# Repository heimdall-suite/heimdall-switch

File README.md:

# heimdall-switch

Wireless power switch node for RC vehicles, part of the [Heimdall Suite](../heimdall-kickoff.md).

Controlled from `heimdall-module` over BLE, independent of the vehicle's
normal RC control link (e.g. CRSF) — this switch has its own out-of-band
radio path so it keeps working regardless of the state of the main control
link. It originated as a replacement for a boat's Jeti SPS-20 magnetic
switch, but is built as a generic building block (not a single-purpose
commercial part like Jeti's RCPS10) so the same design serves any RC
vehicle — boat, plane, car — needing a remotely switched load.

## How it's triggered

```mermaid
flowchart LR
    TX["EdgeTX transmitter<br/>Lua widget or OneClick"]
    BTN["Local button<br/>on the switch node"]
    MOD["heimdall-module<br/>external RF module (ESP32-C3)"]
    SW["heimdall-switch<br/>nRF52 node"]
    LOAD["Switched load"]

    TX -- "S.Port" --> MOD
    MOD -- "BLE command (absolute ON/OFF)" --> SW
    SW -- "MOSFET (fail-on)" --> LOAD
    SW -- "BLE ack burst" --> MOD
    MOD -- "S.Port telemetry (ack)" --> TX
    BTN -. "5-15s: toggle, 15s+: pair" .-> SW
```

The transmitter side (Lua widget or a OneClick action) sends the command
through `heimdall-module`, the external RF module in the transmitter's
module bay; `heimdall-module` relays it over BLE to `heimdall-switch`,
which drives the MOSFET and acks back the same path so the widget can
show "Hello" / "Goodbye" / "No response". The node also has a local button
for manual toggling and pairing, independent of that whole chain.

## Docs

- [.docs/hardware.md](.docs/hardware.md) — MCU, power, switching stage,
  feedback, button/LED, open hardware items
- [.docs/protocol.md](.docs/protocol.md) — BLE roles, pairing, runtime
  cycle, command/ack frame layouts, the transmitter-side Lua widget
- [.docs/persistence.md](.docs/persistence.md) — what's kept in flash
  across power loss (state + replay counter) and the wear-levelling scheme
- [.agents/AGENTS.md](.agents/AGENTS.md) / [CLAUDE.md](CLAUDE.md) —
  instructions for AI coding agents working in this repo
- [hardware/kicad/](hardware/kicad/) — first-draft KiCad schematic (see
  `.docs/hardware.md`'s Schematic section for what's in it and what's
  still a placeholder)

## Status

No firmware yet. nRF52 toolchain (nRF5 SDK vs. nRF Connect SDK/Zephyr vs.
upstream Zephyr) is not yet decided. `src/` is a placeholder until that's
settled. A first-pass schematic exists under `hardware/kicad/`.

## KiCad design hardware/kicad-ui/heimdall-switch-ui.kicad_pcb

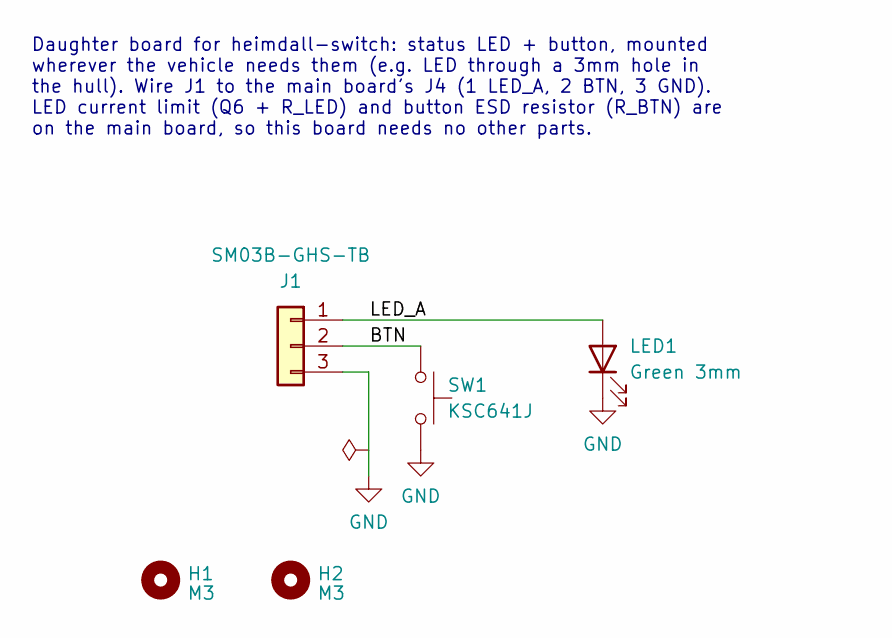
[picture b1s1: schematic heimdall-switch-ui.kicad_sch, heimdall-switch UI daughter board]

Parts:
H1, H2: M3; MountingHole_2.5mm_M3_Tapped
J1: SM03B-GHS-TB; JST_GH_SM03B-GHS-TB_1x03-1MP_P1.25mm_Horizontal; MPN SM03B-GHS-TB(LF)(SN); LCSC C514175
LED1: Green 3mm; LED_D3.0mm; MPN L-7104ZGCK; LCSC C414645
SW1: KSC641J; SW_Push_1P1T_NO_CK_KSC6xxJ; MPN KSC641J LFS; LCSC C226344

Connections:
/BTN: J1.2, SW1.1
/LED_A: J1.1, LED1.2 (A)
GND: J1.3, LED1.1 (K), SW1.2

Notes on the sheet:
Daughter board for heimdall-switch: status LED + button, mounted wherever the vehicle needs them (e.g. LED through a 3mm hole in the hull). Wire J1 to the main board's J4 (1 LED_A, 2 BTN, 3 GND). LED current limit (Q6 + R_LED) and button ESD resistor (R_BTN) are on the main board, so this board nee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

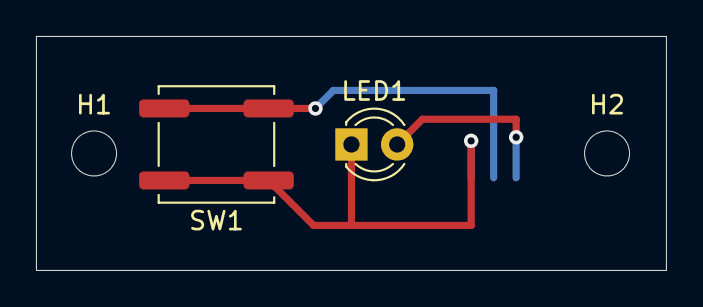
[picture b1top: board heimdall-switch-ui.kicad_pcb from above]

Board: 2 copper layers, 35.0 x 13.0 mm, 5 parts (1 on the bottom side), 3 nets.

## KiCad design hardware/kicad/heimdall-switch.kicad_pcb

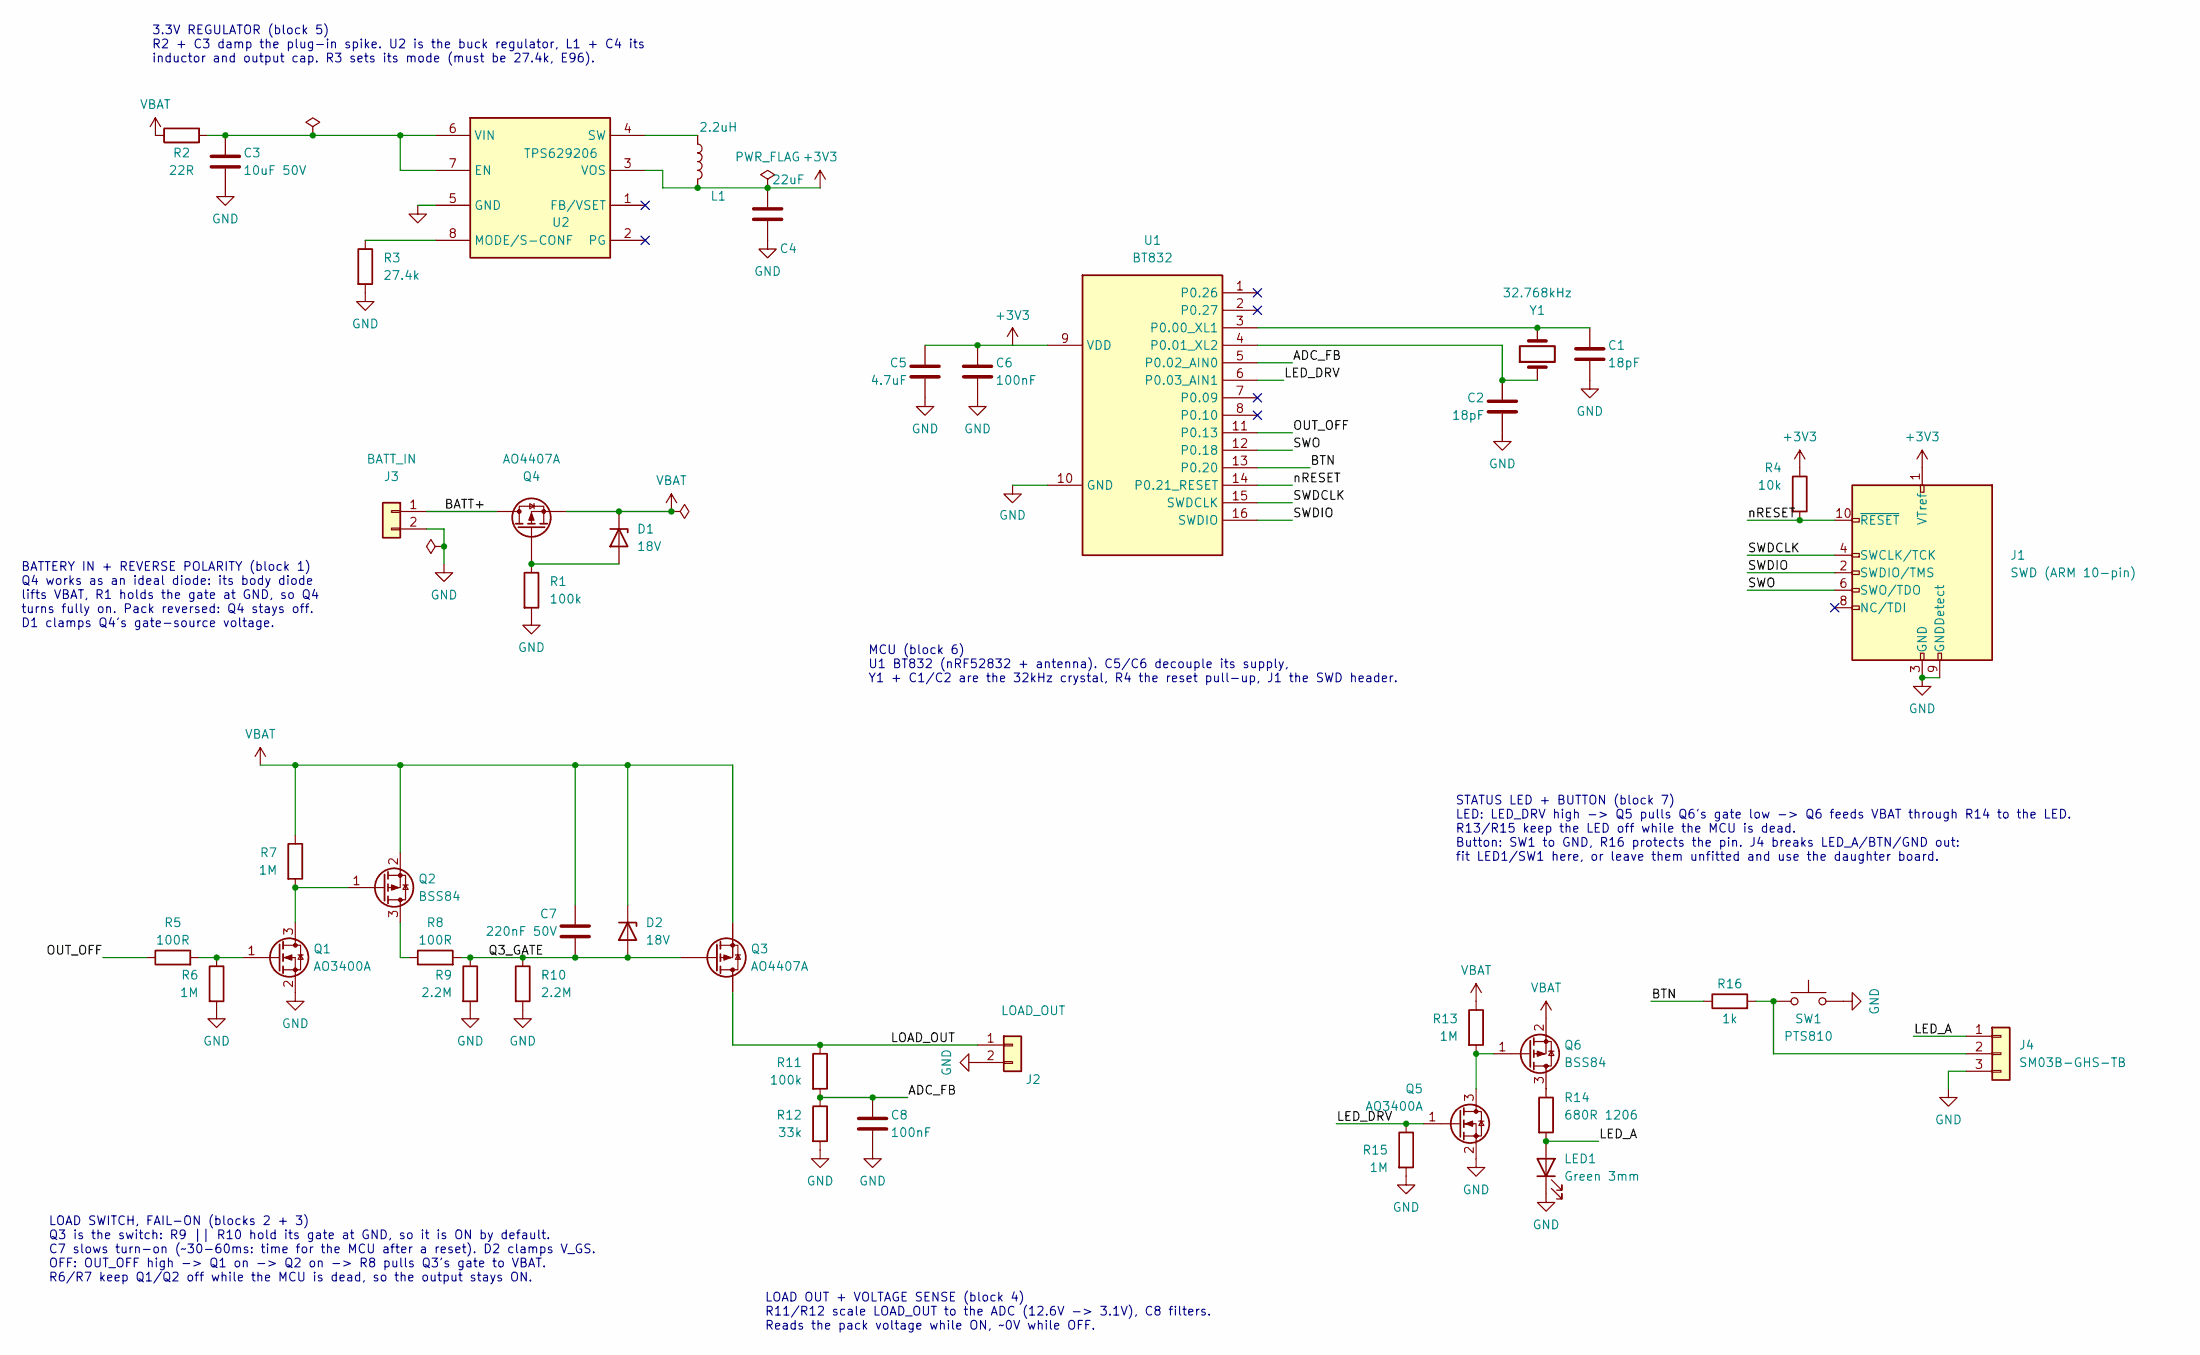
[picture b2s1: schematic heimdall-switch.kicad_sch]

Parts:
C1, C2: 18pF; C_0603_1608Metric; LCSC C1647
C3: 10uF 50V; C_1206_3216Metric; LCSC C89632
C4: 22uF; C_0805_2012Metric; LCSC C45783
C5: 4.7uF; C_0603_1608Metric; LCSC C19666
C6, C8: 100nF; C_0603_1608Metric; LCSC C14663
C7: 220nF 50V; C_0805_2012Metric; LCSC C5378
D1, D2: 18V; D_SOD-123; LCSC C2127
J1: SWD (ARM 10-pin); PinHeader_2x05_P1.27mm_Vertical_SMD; LCSC C41376037
J2: LOAD_OUT; SolderWire-0.75sqmm_1x02_P3.5mm_D1.25mm_OD2.3mm
J3: BATT_IN; SolderWire-0.75sqmm_1x02_P3.5mm_D1.25mm_OD2.3mm
J4: SM03B-GHS-TB; JST_GH_SM03B-GHS-TB_1x03-1MP_P1.25mm_Horizontal; LCSC C514175
L1: 2.2uH; L_1008_2520Metric; LCSC C237482
LED1: Green 3mm; LED_D3.0mm; LCSC C414645
Q1, Q5: AO3400A; SOT-23; LCSC C20917
Q2, Q6: BSS84; SOT-23; LCSC C493579
Q3, Q4: AO4407A; SOIC-8_3.9x4.9mm_P1.27mm; LCSC C16072
R1, R11: 100k; R_0603_1608Metric; LCSC C25803
R2: 22R; R_0603_1608Metric; LCSC C23345
R3: 27.4k; R_0603_1608Metric; LCSC C22964
R4: 10k; R_0603_1608Metric; LCSC C98220
R5, R8: 100R; R_0603_1608Metric; LCSC C22775
R6, R7, R13, R15: 1M; R_0603_1608Metric; LCSC C22935
R9, R10: 2.2M; R_0603_1608Metric; LCSC C22938
R12: 33k; R_0603_1608Metric; LCSC C4216
R14: 680R 1206; R_1206_3216Metric; LCSC C17975
R16: 1k; R_0603_1608Metric; LCSC C21190
SW1: PTS810; SW_SPST_PTS810; LCSC C116501
U1: BT832; Fanstel_BT832
U2: TPS629206; SOT-583-8; LCSC C5219292
Y1: 32.768kHz; Crystal_SMD_3215-2Pin_3.2x1.5mm; LCSC C32346

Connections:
+3V3: C4.1, C5.1, C6.1, J1.1 (VTref), L1.2, R4.1, U1.9 (VDD), U2.3 (VOS)
/ADC_FB: C8.1, R11.2, R12.1, U1.5 (P0.02_AIN0)
/BATT+: J3.1, Q4.5 (D), Q4.6 (D), Q4.7 (D), Q4.8 (D)
/BTN: R16.1, U1.13 (P0.20)
/LED_A: J4.1, LED1.2 (A), R14.2
/LED_DRV: Q5.1 (G), R15.1, U1.6 (P0.03_AIN1)
/LOAD_OUT: J2.1, Q3.5 (D), Q3.6 (D), Q3.7 (D), Q3.8 (D), R11.1
/OUT_OFF: R5.1, U1.11 (P0.13)
/Q3_GATE: C7.2, D2.2 (A), Q3.4 (G), R8.2, R9.1, R10.1
/SWDCLK: J1.4 (SWCLK/TCK), U1.15 (SWDCLK)
/SWDIO: J1.2 (SWDIO/TMS), U1.16 (SWDIO)
/SWO: J1.6 (SWO/TDO), U1.12 (P0.18)
/nRESET: J1.10 (~RESET), R4.2, U1.14 (P0.21_RESET)
GND: C1.2, C2.2, C3.2, C4.2, C5.2, C6.2, C8.2, J1.3 (GND), J1.5 (GND), J1.9 (GNDDetect), J2.2, J3.2, J4.3, LED1.1 (K), Q1.2 (S), Q5.2 (S), R1.2, R3.2, R6.2, R9.2, R10.2, R12.2, R15.2, SW1.2, U1.10 (GND), U2.5 (GND)
unnamed: D1.2 (A), Q4.4 (G), R1.1
unnamed: J4.2, R16.2, SW1.1
unnamed: Q1.3 (D), Q2.1 (G), R7.2
unnamed: Q1.1 (G), R5.2, R6.1
unnamed: Q2.3 (D), R8.1
unnamed: Q5.3 (D), Q6.1 (G), R13.2
unnamed: Q6.3 (D), R14.1
unnamed: C1.1, U1.3 (P0.00_XL1), Y1.2
unnamed: C2.1, U1.4 (P0.01_XL2), Y1.1
unnamed: C3.1, R2.2, U2.6 (VIN), U2.7 (EN)
unnamed: R3.1, U2.8 (MODE/S-CONF)
unnamed: L1.1, U2.4 (SW)
VBAT: C7.1, D1.1 (K), D2.1 (K), Q2.2 (S), Q3.1 (S), Q3.2 (S), Q3.3 (S), Q4.1 (S), Q4.2 (S), Q4.3 (S), Q6.2 (S), R2.1, R7.1, R13.1

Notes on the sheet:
3.3V REGULATOR (block 5) R2 + C3 damp the plug-in spike. U2 is the buck regulator, L1 + C4 its inductor and output cap. R3 sets its mode (must be 27.4k, E96).
BATTERY IN + REVERSE POLARITY (block 1) Q4 works as an ideal diode: its body diode lifts VBAT, R1 holds the gate at GND, so Q4 turns fully on. Pack reversed: Q4 stays off. D1 clamps Q4's gate-source voltage.
LOAD SWITCH, FAIL-ON (blocks 2 + 3) Q3 is the switch: R9 || R10 hold its gate at GND, so it is ON by default. C7 slows turn-on (~30-60ms: time for the MCU after a reset). D2 clamps V_GS. OFF: OUT_OFF high -> Q1 on -> Q2 on -> R8 pulls Q3's gate to VBAT. R6/R7 keep Q1/Q2 off while the MCU is dead, s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
LOAD OUT + VOLTAGE SENSE (block 4) R11/R12 scale LOAD_OUT to the ADC (12.6V -> 3.1V), C8 filters. Reads the pack voltage while ON, ~0V while OFF.
MCU (block 6) U1 BT832 (nRF52832 + antenna). C5/C6 decouple its supply, Y1 + C1/C2 are the 32kHz crystal, R4 the reset pull-up, J1 the SWD header.
STATUS LED + BUTTON (block 7) LED: LED_DRV high -> Q5 pulls Q6's gate low -> Q6 feeds VBAT through R14 to the LED. R13/R15 keep the LED off while the MCU is dead. Button: SW1 to GND, R16 protects the pin. J4 breaks LED_A/BTN/GND out: fit LED1/SW1 here, or leave them unfitted and use the daughter bo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

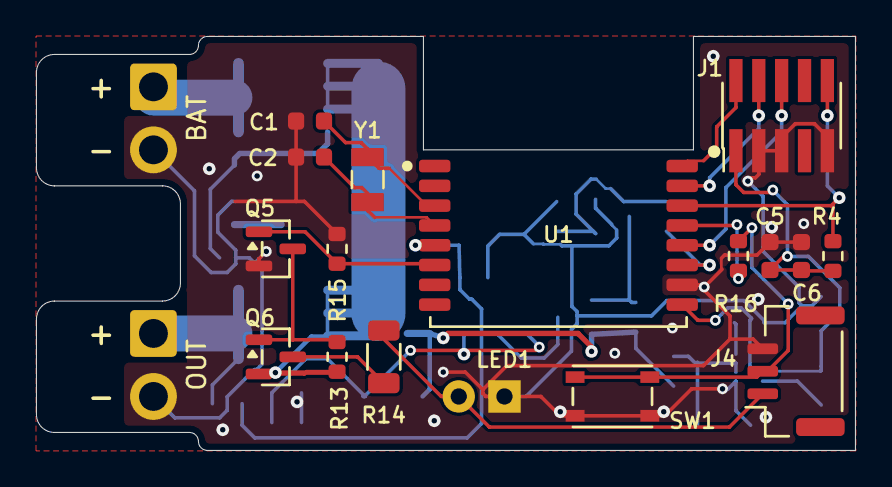
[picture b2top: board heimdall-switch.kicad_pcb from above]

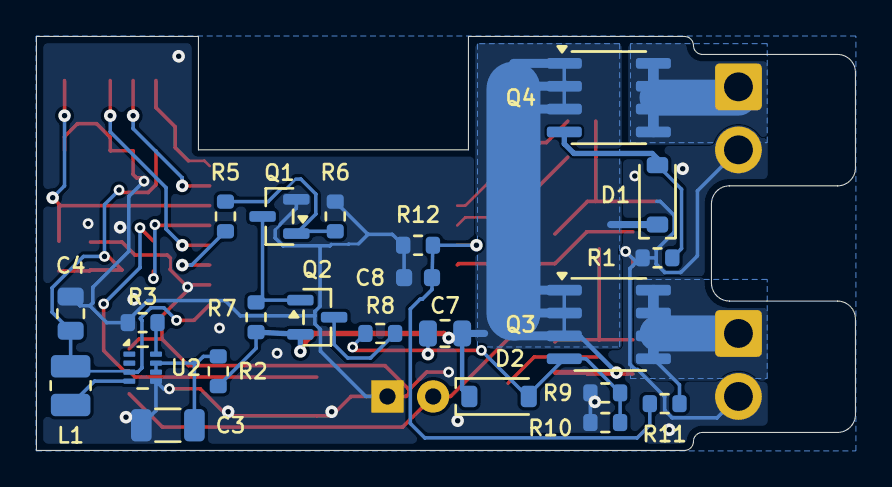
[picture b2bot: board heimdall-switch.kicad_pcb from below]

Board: 2 copper layers, 45.5 x 23.0 mm, 42 parts (23 on the bottom side), 27 nets.
